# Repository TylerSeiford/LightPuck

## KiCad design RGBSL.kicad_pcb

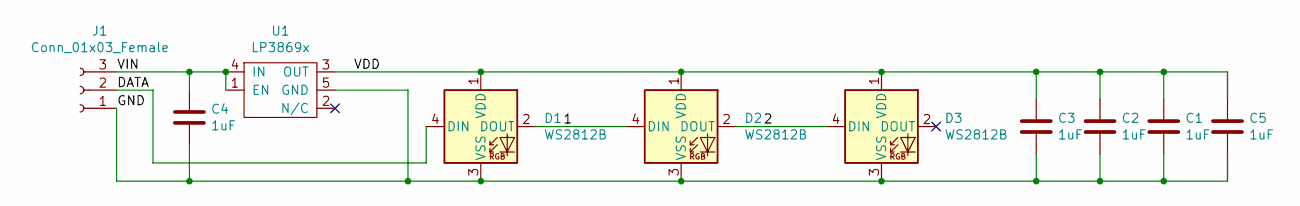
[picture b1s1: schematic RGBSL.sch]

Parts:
C1, C2, C3, C4, C5: 1uF; C_0805_2012Metric_Pad1.15x1.40mm_HandSolder
D1, D2, D3: WS2812B; LED_WS2812B_PLCC4_5.0x5.0mm_P3.2mm
J1: Conn_01x03_Female; PinSocket_1x03_P2.54mm_Vertical
U1: LP3869x; SOT-223-5

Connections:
/1: D1.2 (DOUT), D2.4 (DIN)
/2: D2.2 (DOUT), D3.4 (DIN)
/DATA: D1.4 (DIN), J1.2
/GND: C1.2, C2.2, C3.2, C4.2, C5.2, D1.3 (VSS), D2.3 (VSS), D3.3 (VSS), J1.1, U1.5 (GND)
/VDD: C1.1, C2.1, C3.1, C5.1, D1.1 (VDD), D2.1 (VDD), D3.1 (VDD), U1.3 (OUT)
/VIN: C4.1, J1.3, U1.1 (EN), U1.4 (IN)

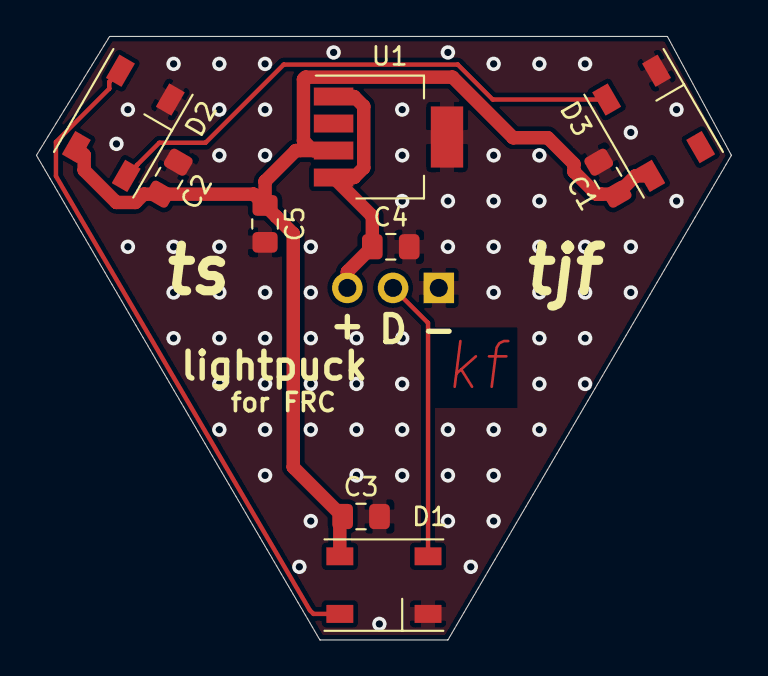
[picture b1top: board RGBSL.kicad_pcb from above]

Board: 2 copper layers, 38.6 x 33.5 mm, 10 parts (1 on the bottom side), 6 nets.

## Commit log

2019-12-07 I got bored again
2019-12-07 Added output cap for linreg
